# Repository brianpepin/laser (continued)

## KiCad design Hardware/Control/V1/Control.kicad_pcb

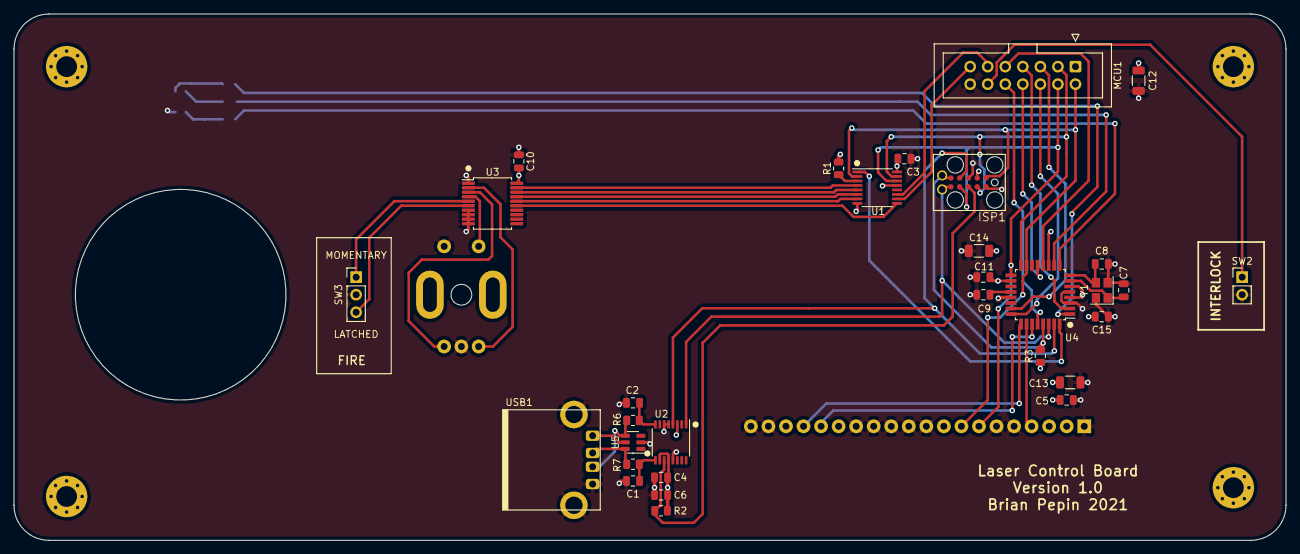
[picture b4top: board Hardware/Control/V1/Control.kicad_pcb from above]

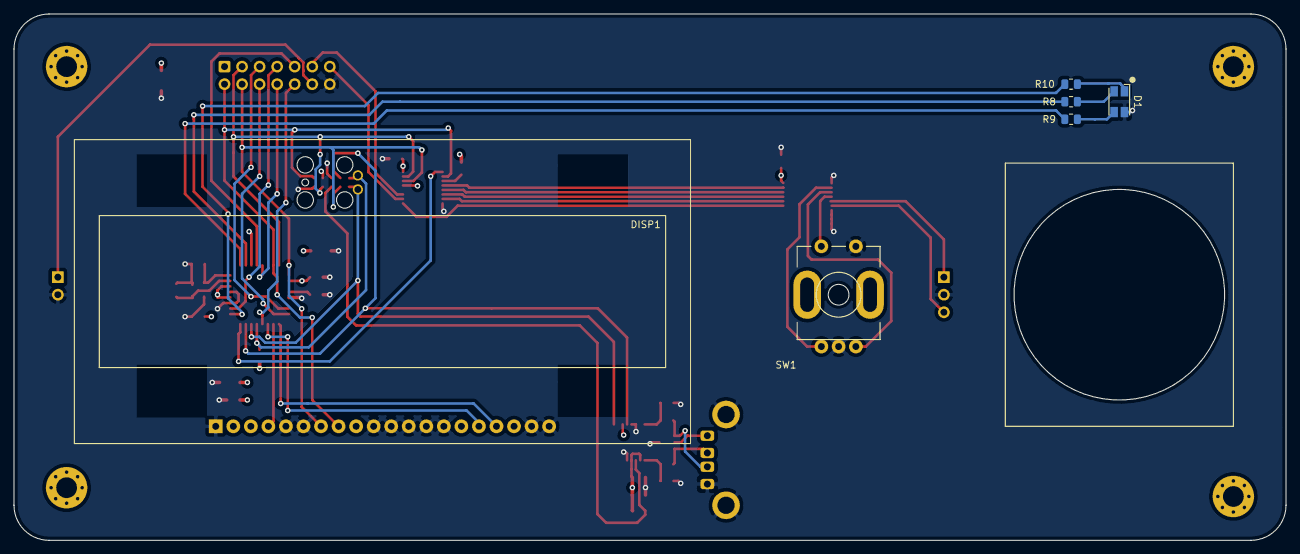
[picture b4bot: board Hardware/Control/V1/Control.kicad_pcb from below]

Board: 4 copper layers, 184.2 x 76.2 mm, 41 parts (6 on the bottom side), 48 nets.

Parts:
C1, C2: 47pF; C_0805_2012Metric
C3, C4, C5, C9, C10, C11, C15: .1uF; C_0805_2012Metric
C6: 4.7uF; C_0805_2012Metric
C7, C8: 18pF; C_0805_2012Metric
C12, C13, C14: 22uF; C_1206_3216Metric
D1: AAA3528LSEKJ3ZGKQBKS; LED_Avago_PLCC4_3.2x2.8mm_CW
DISP1: NHD-3.12-25664UCW2; NHD-3.12-25664UC
H1, H2, H3, H4: MountingHole_Pad; MountingHole_3mm_Pad_Via
ISP1: AVR_ISP_10_SERIAL; TC2050-IDC
MCU1: 2-1761603-5; IDC-Header_2x07_P2.54mm_Vertical
R1, R2, R3: 10k; R_0805_2012Metric
R6, R7: 27; R_0805_2012Metric
R8, R9: 175; R_0805_2012Metric
R10: 600; R_0805_2012Metric
SW1: EN11-HSM1AF20; EN11-HSM
SW2: KO128B2007; PinHeader_1x02_P2.54mm_Vertical
SW3: TRD11G10WL; PinHeader_1x03_P2.54mm_Vertical
U1: XRA1402IG16TR-F; TSSOP-16_4.4x5mm_P0.65mm
U2: FT230XS-U; SSOP-16_3.9x4.9mm_P0.635mm
U3: MAX6818EAP+T; SSOP-20_5.3x7.2mm_P0.65mm
U4: ATMEGA328P-AU; TQFP-32_7x7mm_P0.8mm
U5: ESDALD05UD4; SOT-23-6
USB1: USB-A1HSW6
Y1: ABM8AIG-20.000MHZ-4-T; Crystal_SMD_3225-4Pin_3.2x2.5mm

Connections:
+3V0: C3.2, C4.1, C5.2, C6.1, C10.2, C11.2, C12.1, C13.1, C14.1, C15.1, DISP1.2, ISP1.2, MCU1.1, R1.2, R2.2, R3.1, U1.16, U2.3, U2.10, U2.12, U3.20, U4.4, U4.6, U4.18
BUTTON_IRQ: U1.13, U4.11
CS_BUTTONS: U1.1, U4.32
CS_CHARGE: MCU1.11, U1.11
CS_LASER: MCU1.5, U4.23
CS_TEC_READ: MCU1.9, U4.12
CS_TEC_SET: MCU1.8, U4.13
DISP_CS: DISP1.17, U4.25
DISP_DC: DISP1.4, U4.26
DISP_RES: DISP1.16, U4.27
ENC_A: U1.4, U3.19
ENC_A_SW: SW1.A, U3.2
ENC_B: U1.5, U3.18
ENC_B_SW: SW1.B, U3.3
ENC_SEL: U1.6, U3.17
ENC_SEL_SW: SW1.S1, U3.4
FIRE_LATCH: U1.9, U3.15
FIRE_LATCH_SW: SW3.3, U3.6
FIRE_MOM: U1.7, U3.16
FIRE_MOM_SW: SW3.1, U3.5
GND: C1.2, C2.2, C3.1, C4.2, C5.1, C6.2, C7.2, C8.1, C9.2, C10.1, C11.1, C12.2, C13.2, C14.2, C15.2, D1.2, DISP1.1, DISP1.5, DISP1.6, DISP1.10, DISP1.11, DISP1.12, DISP1.13, DISP1.14, DISP1.19, DISP1.20, ISP1.3, ISP1.10, MCU1.14, SW1.C, SW1.S2, SW2.2, SW3.2, U1.8, U2.5, U2.6, U2.13, U3.1, U3.7, U3.8, U3.9, U3.10, U4.3, U4.5, U4.21, U5.2, USB1.4, USB1.5, Y1.2, Y1.4
INTERLOCK_EN: MCU1.13, U1.10
INTERLOCK_SW: MCU1.12, SW2.1
ISP: ISP1.8, R2.1, U2.11
LED_B: R8.2, U4.10
LED_G: R9.2, U4.9
LED_R: R10.2, U4.1
MISO: ISP1.9, MCU1.3, U1.15, U4.16
MOSI: DISP1.8, ISP1.1, MCU1.2, U1.2, U4.15
unnamed: C9.1, U4.20
unnamed: D1.1, R10.1
unnamed: D1.3, R9.1
unnamed: D1.4, R8.1
unnamed: R1.1, U1.3
unnamed: R6.1, U5.4, USB1.3
unnamed: R7.1, U5.6, USB1.2
unnamed: U5.5, USB1.1
RESET: ISP1.5, R3.2, U4.29
RST_LASER: MCU1.6, U4.24
RXD: ISP1.6, U2.1, U4.30
SCK: DISP1.7, ISP1.7, MCU1.4, U1.14, U4.17
TEC_ENABLE: MCU1.10, U4.28
TMP_LASER: MCU1.7, U4.2
TXD: ISP1.4, U2.4, U4.31
USBD_N: C1.1, R7.2, U2.9
USBD_P: C2.1, R6.2, U2.8
XTAL1: C7.1, U4.7, Y1.1
XTAL2: C8.2, U4.8, Y1.3

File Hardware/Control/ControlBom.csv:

"Id";"Designator";"Package";"Quantity";"Designation";"Supplier and ref";
1;"SW1";"EN11-HSM";1;"EN11-HSM1AF20";;;
2;"H4,H3,H2,H1";"MountingHole_3mm_Pad_Via";4;"MountingHole_Pad";;;
3;"USB1";"USB-A1HSW6";1;"USB-A1HSW6";;;
4;"C10,C15,C11,C9,C5,C4,C3";"C_0805_2012Metric";7;".1uF";;;
5;"U3";"SSOP-20_5.3x7.2mm_P0.65mm";1;"MAX6818EAP+T";;;
6;"D1";"LED_Avago_PLCC4_3.2x2.8mm_CW";1;"AAA3528LSEKJ3ZGKQBKS";;;
7;"U4";"TQFP-32_7x7mm_P0.8mm";1;"ATMEGA328P-AU";;;
8;"Y1";"Crystal_SMD_3225-4Pin_3.2x2.5mm";1;"ABM8AIG-20.000MHZ-4-T";;;
9;"U5";"SOT-23-6";1;"ESDALD05UD4";;;
10;"U2";"SSOP-16_3.9x4.9mm_P0.635mm";1;"FT230XS-U";;;
11;"U1";"TSSOP-16_4.4x5mm_P0.65mm";1;"XRA1402IG16TR-F";;;
12;"SW3";"PinHeader_1x03_P2.54mm_Vertical";1;"TRD11G10WL";;;
13;"SW2";"PinHeader_1x02_P2.54mm_Vertical";1;"KO128B2007";;;
14;"R10";"R_0805_2012Metric";1;"600";;;
15;"R9,R8";"R_0805_2012Metric";2;"175";;;
16;"R7,R6";"R_0805_2012Metric";2;"27";;;
17;"R3,R2,R1";"R_0805_2012Metric";3;"10k";;;
18;"MCU1";"IDC-Header_2x07_P2.54mm_Vertical";1;"2-1761603-5";;;
19;"ISP1";"TC2050-IDC";1;"AVR_ISP_10_SERIAL";;;
20;"DISP1";"NHD-3.12-25664UC";1;"NHD-3.12-25664UCW2";;;
21;"C14,C13,C12";"C_1206_3216Metric";3;"22uF";;;
22;"C8,C7";"C_0805_2012Metric";2;"18pF";;;
23;"C6";"C_0805_2012Metric";1;"4.7uF";;;
24;"C2,C1";"C_0805_2012Metric";2;"47pF";;;

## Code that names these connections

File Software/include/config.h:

#pragma once

namespace Pins
{
    namespace Spi
    {
        constexpr static uint8_t Mosi   = PIN_SPI_MOSI;
        constexpr static uint8_t Miso   = PIN_SPI_MISO;
        constexpr static uint8_t Sck    = PIN_SPI_SCK;
        constexpr static uint8_t Ss     = PIN_SPI_SS;
    }

    namespace Inputs
    {
        // All inputs are interrupt driven and must be on the
        // same port.
        constexpr static uint8_t EncoderA           = PIN3;
        constexpr static uint8_t EncoderB           = PIN2;
        constexpr static uint8_t EncoderSel         = PIN0;
        constexpr static uint8_t Fire               = PIN1;
        constexpr static uint8_t InterlockEnable    = PIN5;
        constexpr static uint8_t OverTemp           = PIN4;
        static PORT_t&           Port               = PORTD;
    }

    namespace Tec
    {
        constexpr static uint8_t CsRead = PIN_PB3;
        constexpr static uint8_t CsSet  = PIN_PB2;
        constexpr static uint8_t Enable = PIN_PB4;
    }

    namespace Laser
    {
        constexpr static uint8_t Cs     = PIN_PB1;
        constexpr static uint8_t Reset  = PIN_PB0;
    }

    namespace Power
    {
        constexpr static uint8_t Cs     = PIN_PB5;
    }

    namespace Led
    {
        constexpr static uint8_t Red    = PIN_PC0;
        constexpr static uint8_t Green  = PIN_PC1;
        constexpr static uint8_t Blue   = PIN_PC2;

        constexpr static uint8_t Fire   = PIN_PC3;
        constexpr static uint8_t Ready  = PIN_PC4;
    }

    namespace Display
    {
        constexpr static uint8_t Cs     = PIN_PE0;
        constexpr static uint8_t Dc     = PIN_PE2;
        constexpr static uint8_t Reset  = PIN_PE1;
    }
}

namespace Limits
{
    namespace Current
    {
        constexpr static float Pump1 = 25;
        constexpr static float Pump2 = 25;
    }

    namespace Voltage
    {
        constexpr static float HiBat = 8.4;
        constexpr static float LowBat = 7.5;
        constexpr static float CriticalBat = 7.0;
    }

    namespace Temperature
    {
        constexpr static float DisconnectLimit = -30;
    }
}

namespace Tolerances
{
    namespace Temperature
    {
        constexpr static float Pump = 3.0;
        constexpr static float Vanadate = 5.0;
        constexpr static float Ktp = 1.5;
    }
}

namespace Defaults
{
    namespace Temperatures
    {
        constexpr static float Pump1 = 28;
        constexpr static float Pump2 = 25;
        constexpr static float Vanadate = 23;
        constexpr static float Ktp = 36;
    }

    namespace Currents
    {
        namespace Tec
        {
            constexpr static float Pump     = 1.0; // 8.4 amps
            constexpr static float Vanadate = .85; // 6 amps
            constexpr static float Ktp      = .75; // 5.5 amps
        }
    }
}

namespace Calibration
{
    namespace LaserMonitor
    {
        constexpr static float Slope = .00562979359477001;
        constexpr static float Offset = 0;
    }

    namespace Battery
    {
        namespace Voltage
        {
            constexpr static float Slope = 0.008974358974358974358974358974359;
            constexpr static float Offset = 0.44871794871794871794871794871795;
        }

        namespace Current
        {
            constexpr static float Slope = 1;
            constexpr static float Offset = 0;
        }
    }

    // Current slew when ramping up the pump current
    namespace Slew
    {
        constexpr static float Step = .5;
        constexpr static uint8_t Delay = 10;
    }
}

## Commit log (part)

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2023-01-22 More images
2025-01-18 Remove macOS files
2025-01-18 V2.0 Software payload
2025-01-18 Actually add V1.1 files
2025-01-18 Move to AVR128DB64 MCU
2025-01-18 Minor hardware fix for control board; requires software changes too
2025-01-21 New control board
2025-01-21 Fix bad footprint for RGG LED
2025-01-22 Cleanup, remove ground spurs from control board
2025-01-25 Minor tweaks
2025-02-15 Allow simulating other boards; ADC calibration
2025-03-18 use faster display mode bc more memory
2025-03-21 Update to kicad 8
2025-04-13 Fixed menus
2025-05-11 Fix adc calibration; cleanup
2025-07-25 recover v1 of driver board
2025-07-25 Ignore backups
2026-06-21 Final updates
